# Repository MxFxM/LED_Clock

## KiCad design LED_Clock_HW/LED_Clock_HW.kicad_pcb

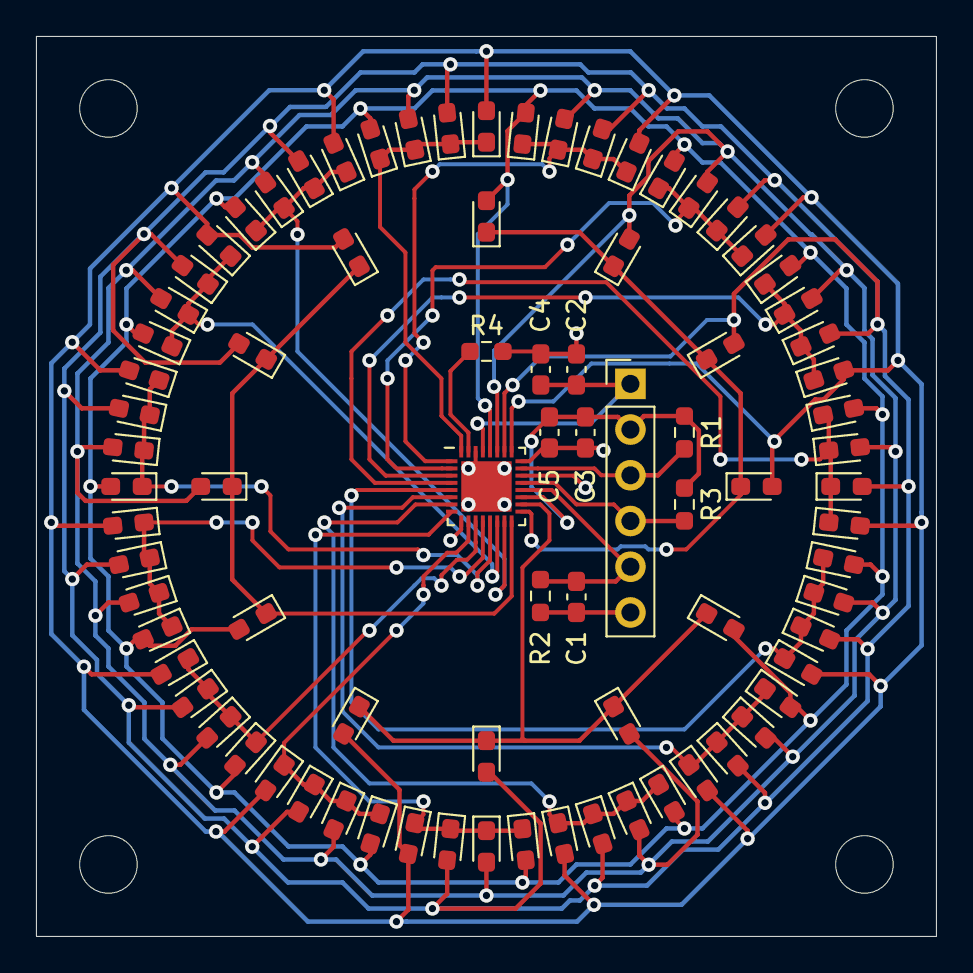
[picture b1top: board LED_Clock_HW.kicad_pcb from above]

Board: 2 copper layers, 50.0 x 50.0 mm, 83 parts (0 on the bottom side), 29 nets.

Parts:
C1, C4, C5: 0u1; C_0603_1608Metric_Pad1.08x0.95mm_HandSolder
C2, C3: 4u7; C_0603_1608Metric_Pad1.08x0.95mm_HandSolder
D1, D2, D3, D4, D5, D6, D7, D8, D9, D10, D11, D12, D13, D14, D15, D16, D17, D18, D19, D20, D21, D22, D23, D24, D25, D26, D27, D28, D29, D30, D31, D32, D33, D34, D35, D36, D37, D38, D39, D40, D41, D42, D43, D44, D45, D46, D47, D48, D49, D50, D51, D52, D53, D54, D55, D56, D57, D58, D59, D60, D61, D62, D63, D64, D65, D66, D67, D68, D69, D70, D71, D72: LED; LED_0603_1608Metric_Pad1.05x0.95mm_HandSolder
J1: Conn_01x06; PinHeader_1x06_P2.54mm_Vertical
R1, R3: 2k2; R_0603_1608Metric_Pad0.98x0.95mm_HandSolder
R2: 100k; R_0603_1608Metric_Pad0.98x0.95mm_HandSolder
R4: 10k; R_0603_1608Metric_Pad0.98x0.95mm_HandSolder
U1: IS31FL3746A; QFN-32_EP_4x4_Pitch0.4mm

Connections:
+3V3: C3.1, C5.1, J1.2, R1.1, R3.1, U1.19
+5V: C2.1, C4.1, J1.1, U1.29
CS1: D1.1, D2.1, D3.1, D4.1, U1.32
CS2: D5.1, D6.1, D7.1, D8.1, U1.1
CS3: D9.1, D10.1, D11.1, D12.1, U1.2
CS4: D13.1, D14.1, D15.1, D16.1, U1.3
CS5: D17.1, D18.1, D19.1, D20.1, U1.4
CS6: D21.1, D22.1, D23.1, D24.1, U1.5
CS7: D25.1, D26.1, D27.1, D28.1, U1.6
CS8: D29.1, D30.1, D31.1, D32.1, U1.7
CS9: D33.1, D34.1, D35.1, D36.1, U1.8
CS10: D37.1, D38.1, D39.1, D40.1, U1.10
CS11: D41.1, D42.1, D43.1, D44.1, U1.11
CS12: D45.1, D46.1, D47.1, D48.1, U1.12
CS13: D49.1, D50.1, D51.1, D52.1, U1.13
CS14: D53.1, D54.1, D55.1, D56.1, U1.14
CS15: D57.1, D58.1, D59.1, D60.1, U1.15
CS16: D61.1, D62.1, D63.1, D64.1, U1.16
CS17: D65.1, D66.1, D67.1, D68.1, U1.17
CS18: D69.1, D70.1, D71.1, D72.1, U1.18
GND: C1.2, C2.2, C3.2, C4.2, C5.2, J1.6, R2.2, R4.2, U1.9, U1.22, U1.24, U1.30, U1.33
unnamed: R4.1, U1.31
SCL: J1.4, R3.2, U1.21
SDA: J1.3, R1.2, U1.23
SDB: C1.1, J1.5, R2.1, U1.20
SW1: D1.2, D5.2, D9.2, D13.2, D17.2, D21.2, D25.2, D29.2, D33.2, D37.2, D41.2, D45.2, D49.2, D53.2, D57.2, D61.2, D65.2, D69.2, U1.28
SW2: D2.2, D6.2, D10.2, D14.2, D18.2, D22.2, D26.2, D30.2, D34.2, D38.2, D42.2, D46.2, D50.2, D54.2, D58.2, D62.2, D66.2, D70.2, U1.27
SW3: D3.2, D7.2, D11.2, D15.2, D19.2, D23.2, D27.2, D31.2, D35.2, D39.2, D43.2, D47.2, D51.2, D55.2, D59.2, D63.2, D67.2, D71.2, U1.26
SW4: D4.2, D8.2, D12.2, D16.2, D20.2, D24.2, D28.2, D32.2, D36.2, D40.2, D44.2, D48.2, D52.2, D56.2, D60.2, D64.2, D68.2, D72.2, U1.25

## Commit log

2022-01-04 done :)
